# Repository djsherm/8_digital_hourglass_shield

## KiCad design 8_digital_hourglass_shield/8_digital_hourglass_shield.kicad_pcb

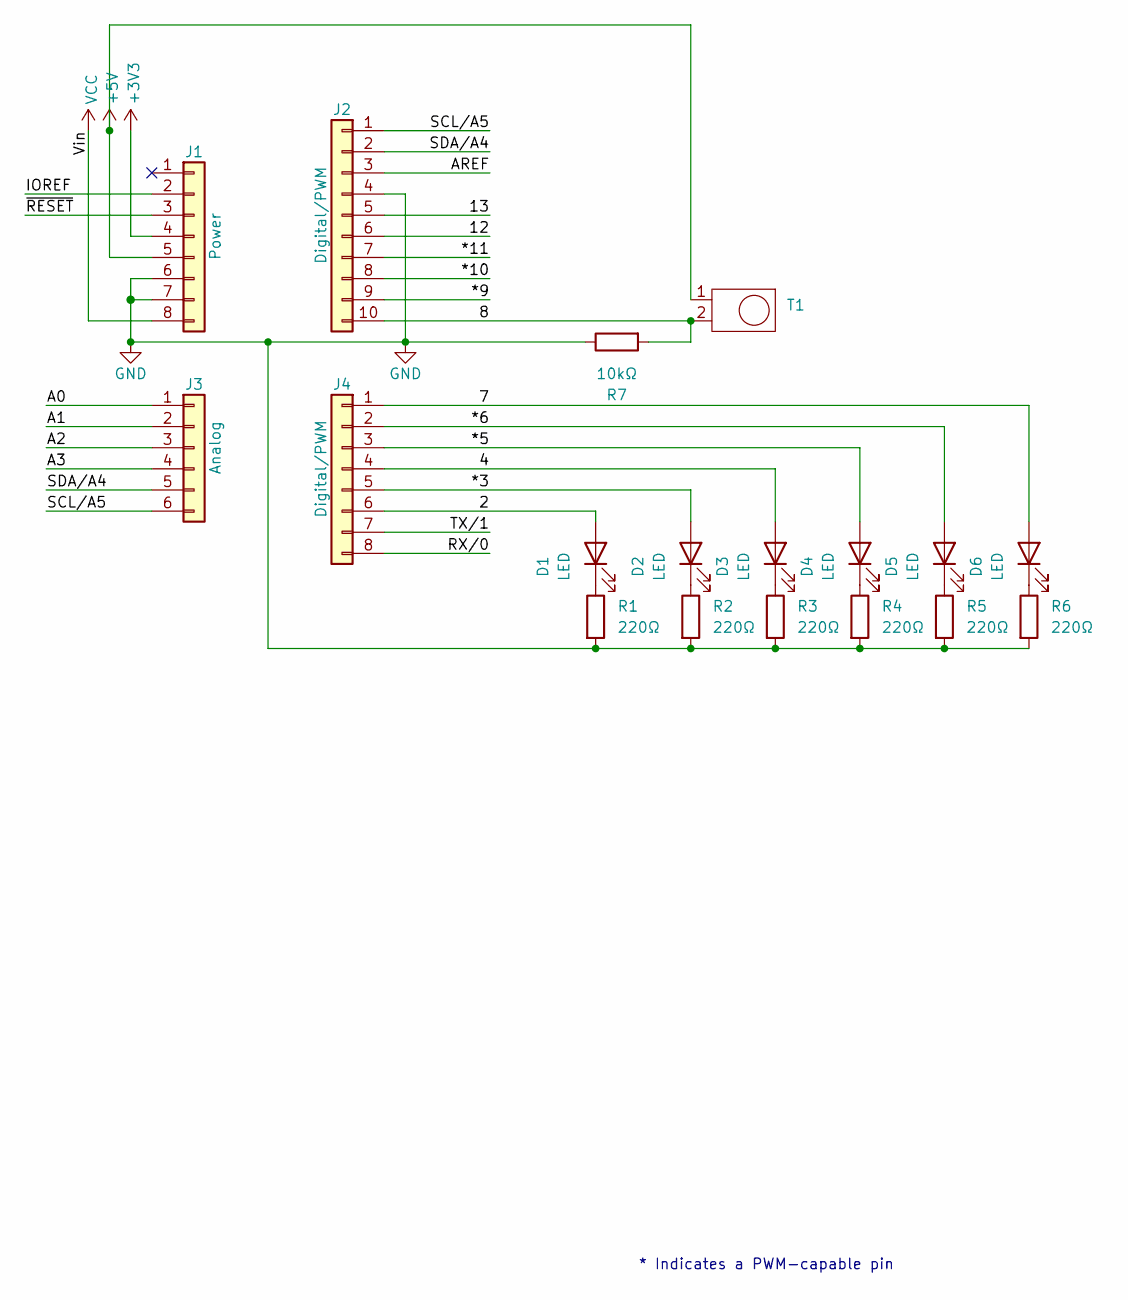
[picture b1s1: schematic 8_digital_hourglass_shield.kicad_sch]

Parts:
D1, D2, D3, D4, D5, D6: LED; LED_D5.0mm_IRGrey
J1: Power; PinSocket_1x08_P2.54mm_Vertical
J2: Digital/PWM; PinSocket_1x10_P2.54mm_Vertical
J3: Analog; PinSocket_1x06_P2.54mm_Vertical
J4: Digital/PWM; PinSocket_1x08_P2.54mm_Vertical
R1, R2, R3, R4, R5, R6: 220Ω; R_Axial_DIN0207_L6.3mm_D2.5mm_P10.16mm_Horizontal
R7: 10kΩ; R_Axial_DIN0207_L6.3mm_D2.5mm_P10.16mm_Horizontal
T1: TILT

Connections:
+3V3: J1.4
+5V: J1.5, T1.1
/2: D1.2 (A), J4.6
/4: D3.2 (A), J4.4
/7: D6.2 (A), J4.1
/8: J2.10, R7.2, T1.2
/12: J2.6
/13: J2.5
/*3: D2.2 (A), J4.5
/*5: D4.2 (A), J4.3
/*6: D5.2 (A), J4.2
/*9: J2.9
/*10: J2.8
/*11: J2.7
/A0: J3.1
/A1: J3.2
/A2: J3.3
/A3: J3.4
/AREF: J2.3
/IOREF: J1.2
/RX/0: J4.8
/SCL/A5: J2.1, J3.6
/SDA/A4: J2.2, J3.5
/TX/1: J4.7
/~RESET: J1.3
GND: J1.6, J1.7, J2.4, R1.2, R2.2, R3.2, R4.2, R5.2, R6.2, R7.1
unnamed: D1.1 (K), R1.1
unnamed: D2.1 (K), R2.1
unnamed: D3.1 (K), R3.1
unnamed: D4.1 (K), R4.1
unnamed: D5.1 (K), R5.1
unnamed: D6.1 (K), R6.1
VCC: J1.8

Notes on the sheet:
* Indicates a PWM-capable pin

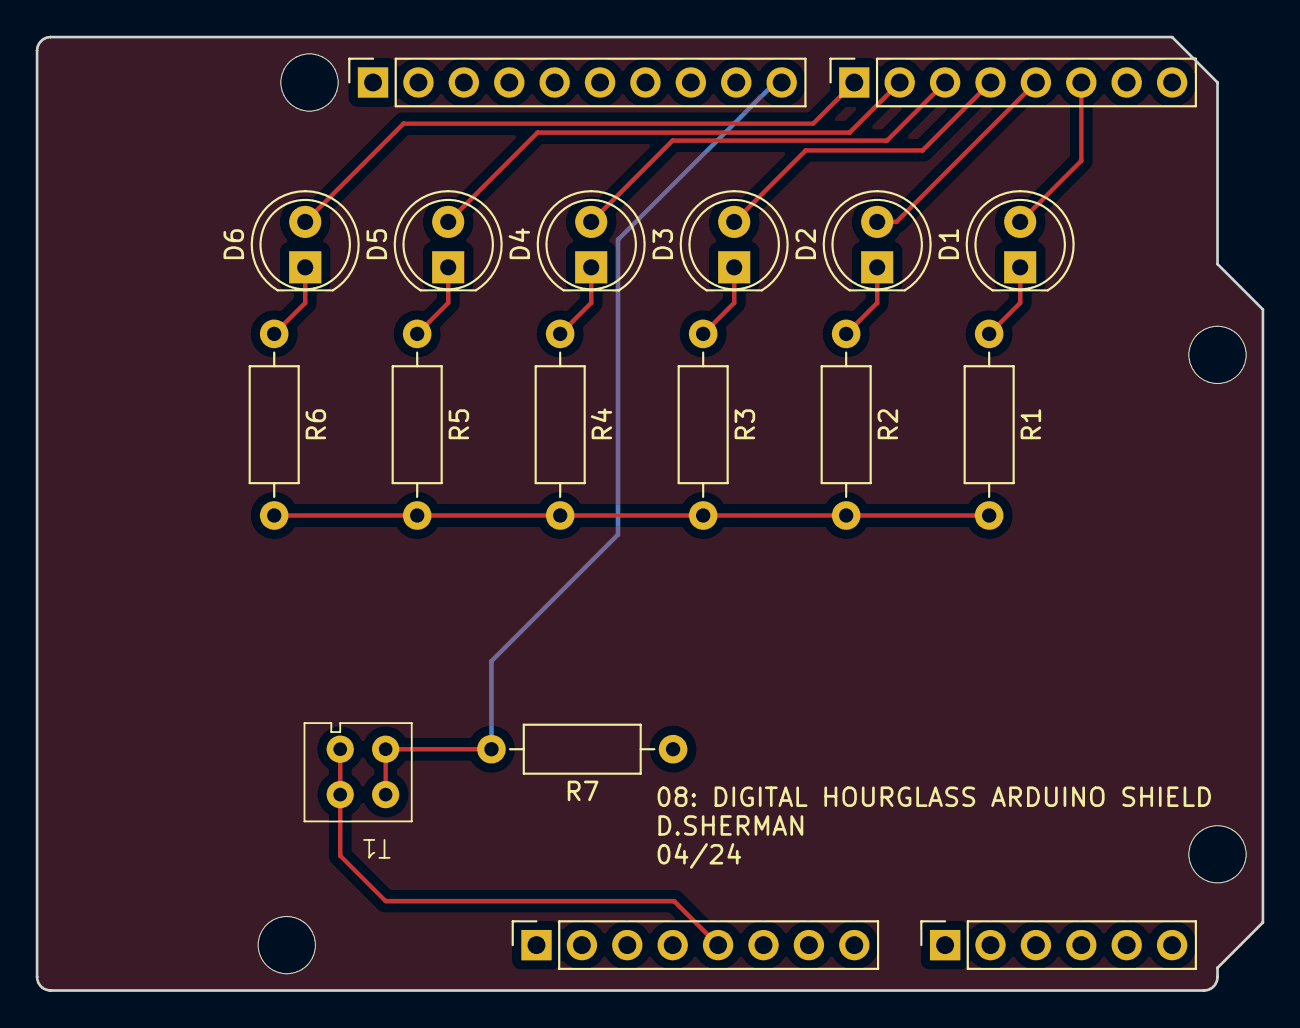
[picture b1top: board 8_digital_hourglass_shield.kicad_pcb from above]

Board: 2 copper layers, 68.6 x 53.3 mm, 22 parts (0 on the bottom side), 17 nets.

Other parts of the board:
MH1, MH2, MH3, MH4: MountingHole_3.2mm
